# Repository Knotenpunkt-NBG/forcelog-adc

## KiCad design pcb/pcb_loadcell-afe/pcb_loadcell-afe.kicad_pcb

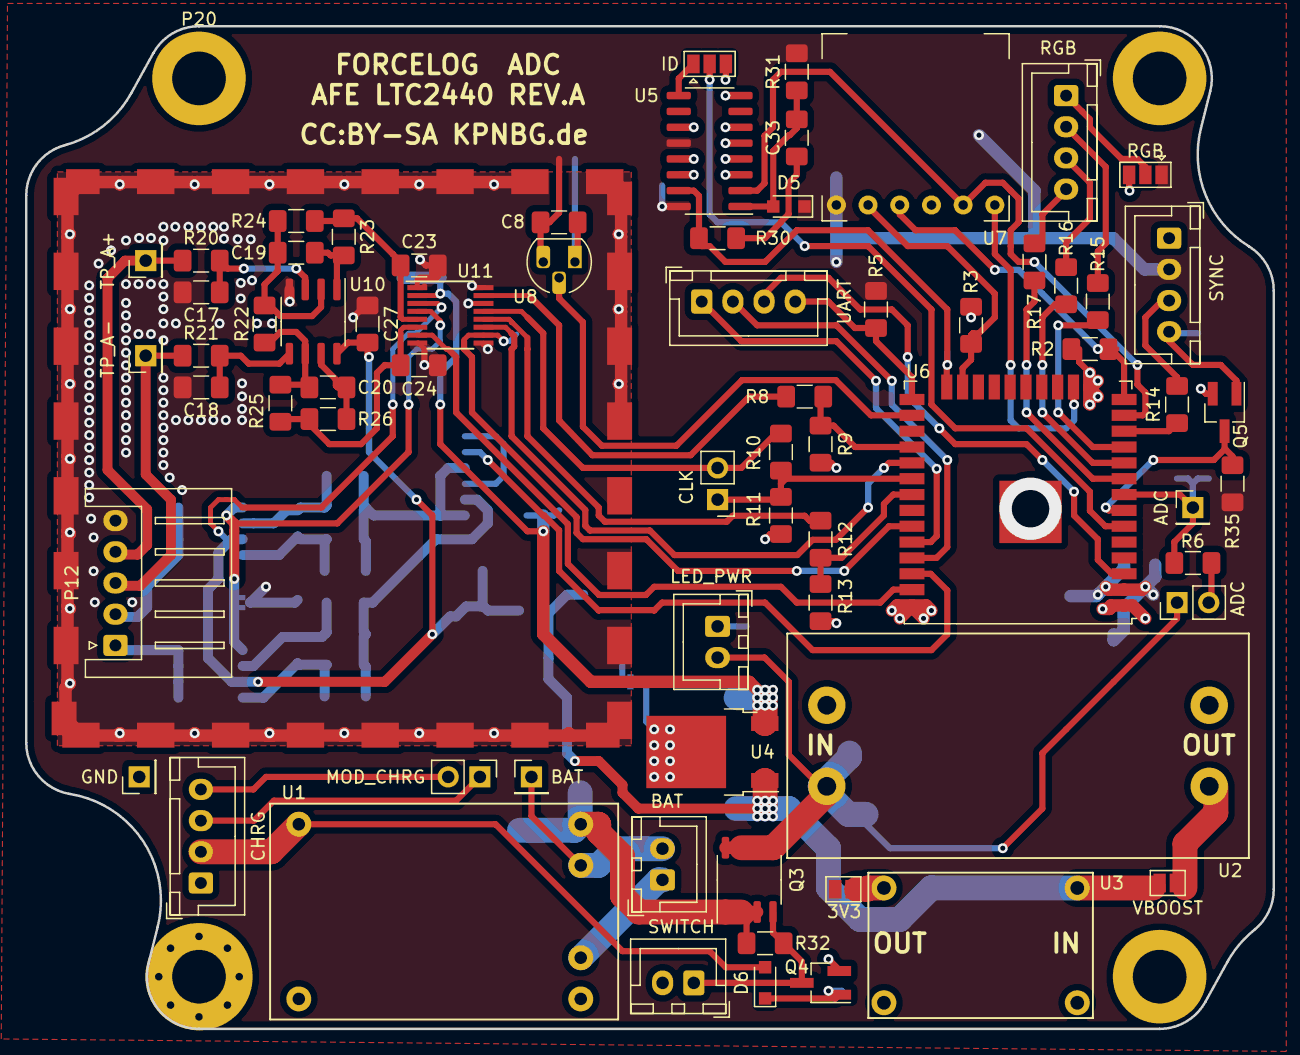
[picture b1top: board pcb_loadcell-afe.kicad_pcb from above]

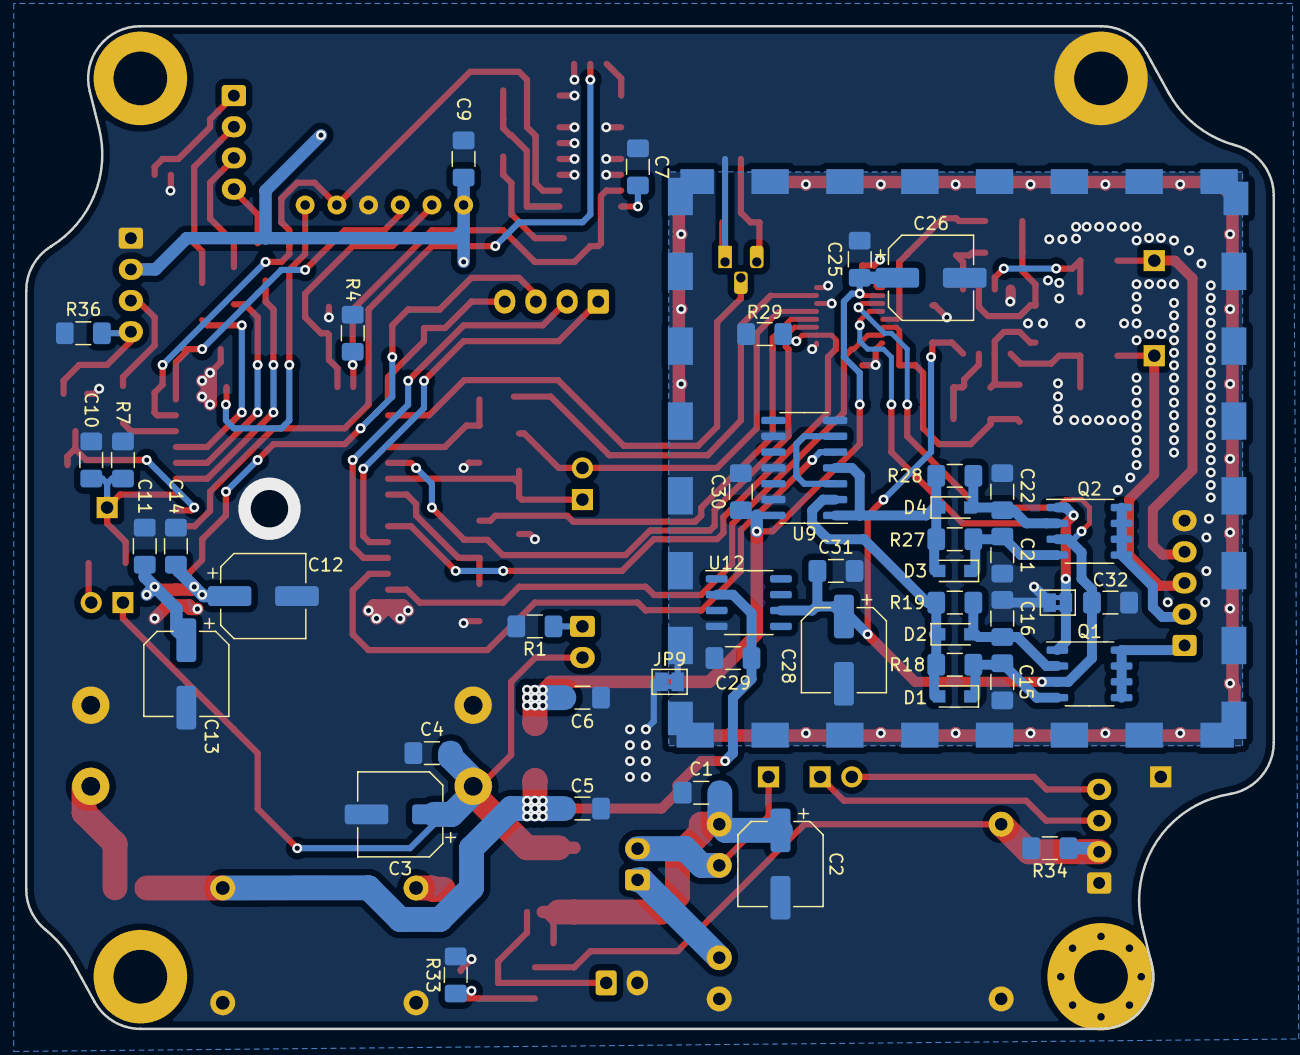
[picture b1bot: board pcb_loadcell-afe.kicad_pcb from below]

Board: 4 copper layers, 100.0 x 80.4 mm, 120 parts (46 on the bottom side), 75 nets.

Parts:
C1, C4, C6, C7, C8, C9, C10, C11, C14, C25, C27, C30, C32, C33: 100n; C_1206_3216Metric_Pad1.42x1.75mm_HandSolder
C2, C3, C12, C13, C26, C28: 10µ; CP_Elec_6.3x5.7
C5: 330n; C_1206_3216Metric_Pad1.42x1.75mm_HandSolder
C15, C16, C21, C22: 1n; C_1206_3216Metric_Pad1.42x1.75mm_HandSolder
C17, C18: 82n; C_1206_3216Metric_Pad1.42x1.75mm_HandSolder
C19, C20: 47n; C_1206_3216Metric_Pad1.42x1.75mm_HandSolder
C23, C24, C29: 1µ; C_1206_3216Metric_Pad1.42x1.75mm_HandSolder
C31: 2µ2; C_1206_3216Metric_Pad1.42x1.75mm_HandSolder
D1, D2, D3, D4, D5: BAT54; D_SOD-323_HandSoldering
D6: 1N4148; D_SOD-323_HandSoldering
JP1: VBOOST; SolderJumper-2_P1.3mm_Open_Pad1.0x1.5mm
JP2: 3V3; SolderJumper-2_P1.3mm_Open_Pad1.0x1.5mm
JP3: ID; SolderJumper-3_P1.3mm_Open_Pad1.0x1.5mm
JP6: ADC; PinHeader_1x02_P2.54mm_Vertical
JP7: CLK; PinHeader_1x02_P2.54mm_Vertical
JP8: RGB; SolderJumper-3_P1.3mm_Open_Pad1.0x1.5mm
JP9: Jumper_2_Bridged; SolderJumper-2_P1.3mm_Bridged2Bar_Pad1.0x1.5mm
JP10: SolderJumper_2_Bridged; SolderJumper-2_P1.3mm_Bridged2Bar_Pad1.0x1.5mm
P1: GND; PinHeader_1x01_P2.54mm_Vertical
P2: BAT; JST_XH_B2B-XH-A_1x02_P2.50mm_Vertical
P3: BAT; PinHeader_1x01_P2.54mm_Vertical
P4: CHRG; JST_XH_B4B-XH-A_1x04_P2.50mm_Vertical
P5: MOD_CHRG; PinHeader_1x02_P2.54mm_Vertical
P6: SWITCH; JST_XH_B2B-XH-A_1x02_P2.50mm_Vertical
P7: LED_PWR; JST_XH_B2B-XH-A_1x02_P2.50mm_Vertical
P8: ADC; PinHeader_1x01_P2.54mm_Vertical
P9: UART; JST_XH_B4B-XH-A_1x04_P2.50mm_Vertical
P10: 4P; JST_XH_B4B-XH-A_1x04_P2.50mm_Vertical
P11: RGB; JST_XH_B4B-XH-A_1x04_P2.50mm_Vertical
P12: CELL; JST_XH_S5B-XH-A_1x05_P2.50mm_Horizontal
P13: TP_A+; PinHeader_1x01_P2.54mm_Vertical
P14: TP_A-; PinHeader_1x01_P2.54mm_Vertical
P15, P16: SHIELD; Shield_TE2118726-2
P17: MNT_ins; MountingHole_4.3mm_M4_Pad_Via
P18, P19: MNT_ins; MountingHole_4.3mm_M4_DIN965_Pad
P20: MNT_shield; MountingHole_4.3mm_M4_DIN965_Pad
Q1, Q2: IRF7343PBF; SO-8_3.9x4.9mm_P1.27mm
Q3: Si4403DDY; SO-8_3.9x4.9mm_P1.27mm
Q4, Q5: 2N7002; SOT-23_Handsoldering
R1: 270; R_1206_3216Metric_Pad1.42x1.75mm_HandSolder
R2, R3, R4, R5, R18, R19, R27, R28, R29, R31, R32, R33, R34, R35, R36: 10k; R_1206_3216Metric_Pad1.42x1.75mm_HandSolder
R6: 750; R_1206_3216Metric_Pad1.42x1.75mm_HandSolder
R7: 1k5; R_1206_3216Metric_Pad1.42x1.75mm_HandSolder
R8, R10, R12, R30: 470; R_1206_3216Metric_Pad1.42x1.75mm_HandSolder
R9, R11, R13: 910; R_1206_3216Metric_Pad1.42x1.75mm_HandSolder
R14, R17: 22; R_1206_3216Metric_Pad1.42x1.75mm_HandSolder
R15: 120; R_1206_3216Metric_Pad1.42x1.75mm_HandSolder
R16: 91; R_1206_3216Metric_Pad1.42x1.75mm_HandSolder
R20, R21, R22: 100; R_1206_3216Metric_Pad1.42x1.75mm_HandSolder
R23, R26: 10; R_1206_3216Metric_Pad1.42x1.75mm_HandSolder
R24, R25: 1k; R_1206_3216Metric_Pad1.42x1.75mm_HandSolder
U1: TP4056withprotect; TP4056_module_prot
U2: BoostConverter; MT3608_module_boost
U3: BuckConverter; dsn-mini-360_buck
U4: 7805; TO-252-2
U5: 74HC165; SOIC-16_3.9x9.9mm_P1.27mm
U6: ESP32-WROOM-32U
U7: W25Q128; W25Q128-module
U8: DS18B20; TO-92_HandSolder
U9: 74HCT14; SOIC-14_3.9x8.7mm_P1.27mm
U10: LT1492; SO-8_3.9x4.9mm_P1.27mm
U11: LTC2440CGN; QSOP-16_3.9x4.9mm_P0.635mm
U12: lt1461; SO-8_3.9x4.9mm_P1.27mm

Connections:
+3V3: C7.1, C8.1, C9.1, C11.1, C12.1, C13.1, C14.1, D5.K, JP2.2, JP8.1, P10.2, R5.2, R31.1, R35.2, U5.12, U5.16, U6.2, U7.1, U8.3
+5V: C6.1, C25.1, C26.1, C30.1, U4.3, U9.14, U11.2
+5VA: C27.1, C28.1, C31.1, C32.1, Q1.3, Q2.3, U10.8, U11.3, U12.6
+BATT: C3.1, C4.1, JP6.1, P7.2, Q3.5, Q3.6, Q3.7, Q3.8, U2.2
/Analog/EX+: P12.1, Q1.5, Q1.6, Q1.7, Q1.8
/Analog/EX-: P12.2, Q2.5, Q2.6, Q2.7, Q2.8
/Analog/MISO: R12.2, U11.12
/BUSY: R8.2, U11.15
/CLK: JP7.2, R10.2, U11.13
/Digital/BLUE: R17.1, U6.9
/Digital/DQ: U6.26, U8.2
/Digital/DTR: P9.4, R5.1, U6.25
/Digital/GREEN: R16.1, U6.10
/Digital/HCLK: U5.2, U6.13, U7.5
/Digital/HMISO: R2.1, U6.14, U7.3
/Digital/HMOSI: U6.16, U7.6
/Digital/H~CS: R3.1, U6.23, U7.2
/Digital/PING: R14.2, U6.12
/Digital/QH: JP3.2, U6.6
/Digital/RED: R15.1, U6.11
/Digital/RTS: P9.3, U6.3
/Digital/RXD: P9.1, U6.34
/Digital/SH: R4.2, R30.1, U5.15, U6.24
/Digital/TRIG: Q5.3, R35.1, U6.7
/Digital/TXD: P9.2, U6.35
/Digital/VBUSY: R8.1, R9.2, U6.28
/Digital/VCLK: JP7.1, R10.1, R11.2, U6.30
/Digital/VMISO: R12.1, R13.2, U6.31
/HBRIDGE: U6.36, U9.5
/MOSI: U6.37, U11.7
/VBOOST: C5.1, C29.1, JP1.2, U3.1, U4.1, U12.2
/~CS: U6.29, U11.11
/~EXT: R29.1, U6.33, U11.10
GND: C1.2, C2.2, C3.2, C4.2, C5.2, C6.2, C7.2, C8.2, C9.2, C10.2, C11.2, C12.2, C13.2, C14.2, JP3.3, JP8.3, JP9.1, P1.1, P4.1, P6.2, P10.1, P20.1, Q4.2, Q5.2, R1.2, R2.2, R3.2, R4.1, R7.1, R9.1, R11.1, R13.1, R33.2, R34.2, R36.1, U1.2, U1.3, U2.1, U2.4, U3.2, U3.4, U4.2, U5.3, U5.4, U5.5, U5.6, U5.8, U5.11, U5.13, U5.14, U6.1, U6.15, U6.38, U6.39, U7.4, U8.1
GNDA: C15.2, C16.2, C17.2, C18.2, C21.2, C22.2, C23.2, C24.2, C25.2, C26.2, C27.2, C28.2, C29.2, C30.2, C31.2, C32.2, JP9.2, JP10.2, P12.5, P15.1, P16.1, R29.2, U9.7, U9.9, U9.11, U9.13, U10.4, U11.1, U11.8, U11.9, U11.14, U11.16, U12.4
unnamed: C1.1, C2.1, Q3.1, Q3.2, Q3.3, R32.1, U1.6
unnamed: C10.1, P8.1, R6.1, R7.2, U6.8
unnamed: C15.1, D1.K, Q1.4, R18.1
unnamed: C16.1, D2.A, Q1.2, R19.1
unnamed: C17.1, R20.2, U10.3
unnamed: C18.1, R21.2, U10.5
unnamed: C19.1, R23.1, U10.1
unnamed: C19.2, R22.2, R24.1, U10.2
unnamed: C20.1, R22.1, R25.1, U10.6
unnamed: C20.2, R26.1, U10.7
unnamed: C21.1, D3.K, Q2.4, R27.2
unnamed: C22.1, D4.A, Q2.2, R28.2
unnamed: C23.1, R23.2, R24.2, U11.5
unnamed: C24.1, R25.2, R26.2, U11.6
unnamed: C33.1, D5.A, R31.2, U5.1
unnamed: C33.2, R30.2
unnamed: D1.A, D2.K, R18.2, R19.2, U9.2
unnamed: D3.A, D4.K, R27.1, R28.1, U9.1, U9.4
unnamed: D6.A, P4.2, R34.1, U1.1
unnamed: D6.K, Q4.1, R33.1
unnamed: JP1.1, U2.3
unnamed: JP2.1, U3.3
unnamed: JP3.1, U5.9
unnamed: JP6.2, R6.2
unnamed: JP8.2, P11.1
unnamed: JP10.1, Q1.1, Q2.1, U11.4
unnamed: P2.1, U1.4
unnamed: P2.2, P3.1, U1.5
unnamed: P4.3, P5.1
unnamed: P4.4, P5.2
unnamed: P6.1, Q3.4, Q4.3, R32.2
unnamed: P7.1, R1.1
unnamed: P10.3, R14.1
unnamed: P10.4, Q5.1, R36.2
unnamed: P11.2, R15.2
unnamed: P11.3, R16.2
unnamed: P11.4, R17.2
unnamed: P12.3, P14.1, R21.1
unnamed: P12.4, P13.1, R20.1
unnamed: U9.3, U9.6

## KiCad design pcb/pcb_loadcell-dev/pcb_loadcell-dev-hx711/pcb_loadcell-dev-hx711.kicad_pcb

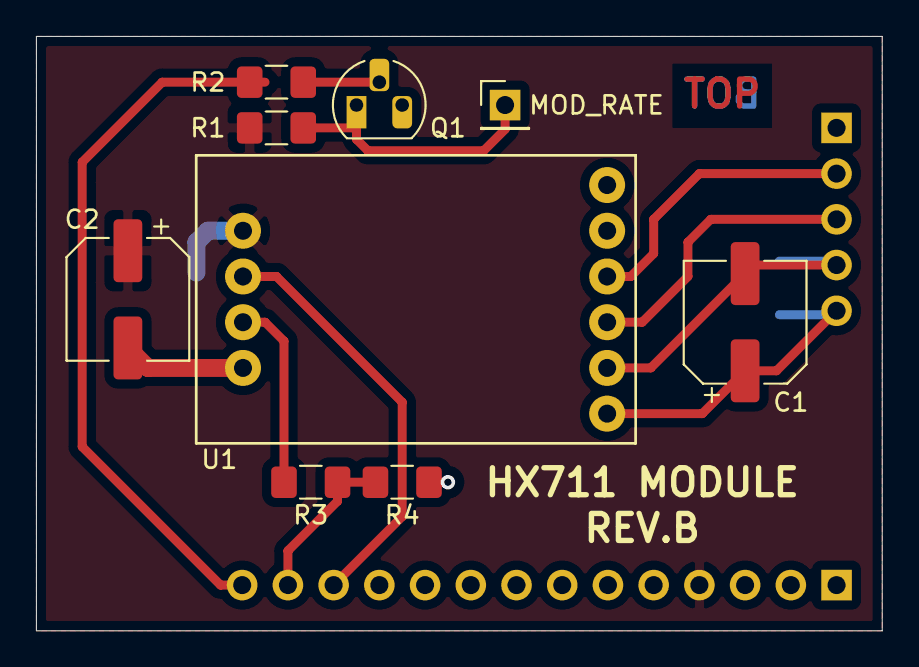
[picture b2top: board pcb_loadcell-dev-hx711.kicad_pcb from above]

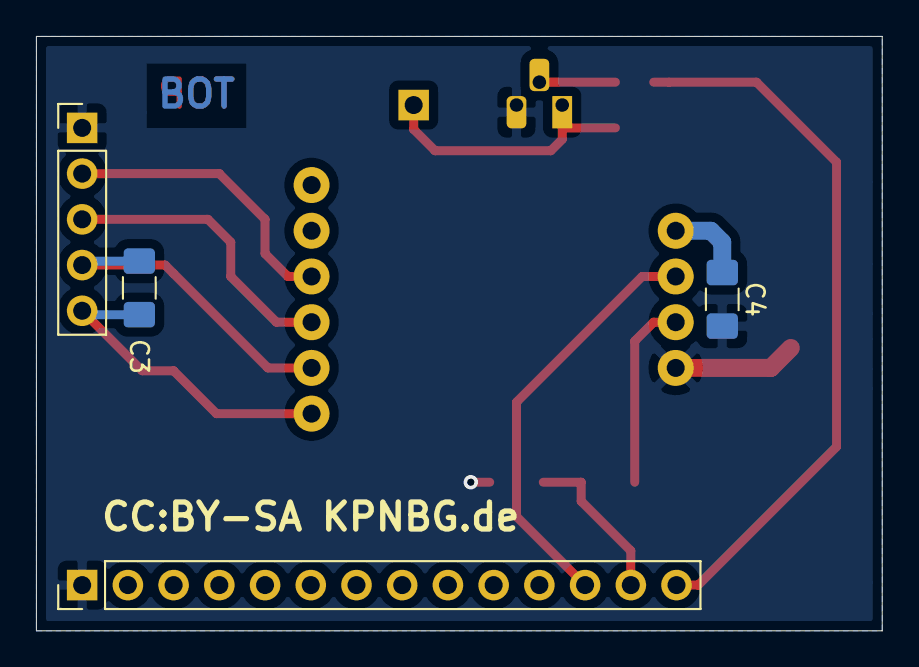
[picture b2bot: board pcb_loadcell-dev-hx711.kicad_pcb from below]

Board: 2 copper layers, 47.0 x 33.0 mm, 13 parts (4 on the bottom side), 12 nets.

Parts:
C1, C2: 10µ; CP_Elec_6.3x5.7
C3, C4: 100n; C_1206_3216Metric_Pad1.42x1.75mm_HandSolder
P1: MOD_RATE; PinHeader_1x01_P2.54mm_Vertical
P2: CONN_01X05; PinHeader_1x05_P2.54mm_Vertical
P3: CONN_01X14; PinHeader_1x14_P2.54mm_Vertical
Q1: BC546; TO-92_HandSolder
R1: 10k; R_1206_3216Metric_Pad1.42x1.75mm_HandSolder
R2: 100; R_1206_3216Metric_Pad1.42x1.75mm_HandSolder
R3: 470; R_1206_3216Metric_Pad1.42x1.75mm_HandSolder
R4: 910; R_1206_3216Metric_Pad1.42x1.75mm_HandSolder
U1: HX711; hx711

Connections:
+5VA: C2.1, C4.1, P3.4, R1.2, U1.7
/A+: P2.3, U1.3
/A-: P2.2, U1.4
/EX+: C1.1, C3.1, P2.5, U1.1
/EX-: C1.2, C3.2, P2.4, U1.2
/IO18: P3.12, U1.8
/IO19: P3.13, R3.1, R4.2
/IO23: P3.14, R2.1
GND: C2.2, C4.2, P2.1, P3.1, Q1.3, R4.1, U1.10
unnamed: P1.1, Q1.1, R1.1
unnamed: Q1.2, R2.2
unnamed: R3.2, U1.9

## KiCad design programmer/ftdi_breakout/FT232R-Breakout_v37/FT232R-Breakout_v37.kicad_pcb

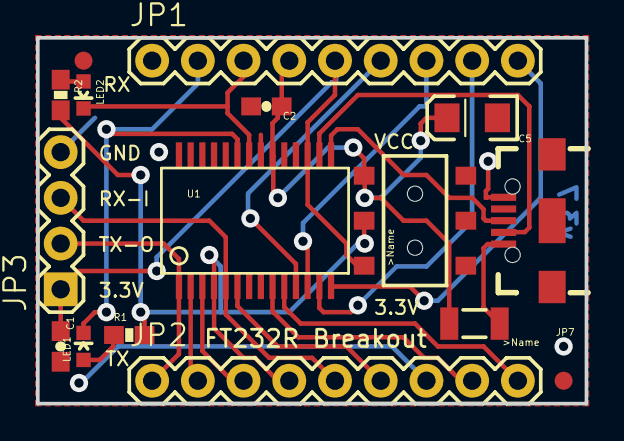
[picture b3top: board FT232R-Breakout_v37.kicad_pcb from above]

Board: 2 copper layers, 30.5 x 20.3 mm, 20 parts (0 on the bottom side), 22 nets.

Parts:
C1, C2: 0.1uF; 0603-CAP
C5: 10uF; EIA3216
F1: 500mA; PTC-1206
FRAME1: FRAME-LETTER; CREATIVE_COMMONS
JP1, JP2: M09; 1X09
JP3: M04PTH; 1X04
JP5, JP6: FIDUCIAL1X2; FIDUCIAL-1X2
JP7: USB_MICROB_PLUGCONN-11752; USB-B-MICRO-SMD_V03
LED1: Red; LED-0603
LED2: Green; LED-0603
LOGO1: OSHW-LOGOS; OSHW-LOGO-S
R1, R2: 330; 0603-RES
S1: SWITCH-SPDTSMD; AYZ0202
U1: FT232R; SSOP28DB
U$1: REVISION
U$2: LOGO-SFENEW; SFE-NEW-WEBLOGO

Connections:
3.3V: C1.1, JP1.5, JP3.1, S1.1, U1.17
/CTS: JP1.6, U1.11
/DCD: JP2.9, U1.10
/DSR: JP2.8, U1.9
/DTR: JP2.2, U1.2
/PWREN: JP1.9, U1.14
/RI: JP2.6, U1.6
/RTS: JP2.3, U1.3
/RXD: JP2.5, JP3.3, U1.5
/RXLED: JP1.3, LED2.C, U1.22
/SLEEP: JP1.7, U1.12
/TXD: JP2.1, JP3.2, U1.1
/TXDEN: JP1.8, U1.13
/TXLED: JP1.2, LED1.C, U1.23
/USB_D+: JP7.D+1, U1.15
/USB_D-: JP7.D-1, U1.16
GND: C1.2, C2.2, C5.C, JP1.1, JP2.7, JP3.4, JP7.GND1, U1.7, U1.18, U1.21, U1.25, U1.26
unnamed: F1.1, JP7.VBUS1
unnamed: LED1.A, R1.1
unnamed: LED2.A, R2.1
VCC: C2.1, C5.A, F1.2, JP1.4, S1.3, U1.20
VCCIO: JP2.4, R1.2, R2.2, S1.2, U1.4

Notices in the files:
parts and their libraries:
Released under the Creative Commons Attribution Share-Alike 3.0 License
